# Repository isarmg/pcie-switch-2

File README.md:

# PCIe switch PCB 设计草案

本仓库保存 KiCad 工程、封装、三维模型、生成及检查脚本，以及历次设计版本。

## 当前 E1.S 版本：Rev W

- [打开 KiCad 工程](outputs/PCIe_E1S_96x45_USB12mm_RevW/Main_12E1S/Main_12E1S.kicad_pro)
- [PCB 源文件](outputs/PCIe_E1S_96x45_USB12mm_RevW/Main_12E1S/Main_12E1S.kicad_pcb)
- [STEP 模型](outputs/PCIe_E1S_96x45_USB12mm_RevW/Main_12E1S/Main_12E1S.step)
- [设计说明与限制](outputs/PCIe_E1S_96x45_USB12mm_RevW/README.md)
- [当前重新审查](outputs/PCIe_E1S_96x45_USB12mm_RevW/rebuild_review_2026-10-18/README.md)

板框 96 × 45 mm，12 个竖直 E1.S 插槽，中心距 8 mm。按 CPU/switch 面看，主要顺序为左侧 USB-C、中部 CPU、右侧 switch；供电 USB-C 中心距左板边 12 mm，雷电口为 24 mm，两口中心距 12 mm，均位于板高 22.5 mm。

CPU 为 Ultra 9 288V / 32 GB 封装内存版本；switch 使用经授权虚构的 PEX90064 球位及 33 × 33 mm 封装。雷电电路仍采用雷电 3 主机口方案。32 层叠层和过孔结构是布局布线假设。

历史第一轮的本地电气修订见 [历史审查](outputs/PCIe_E1S_96x45_USB12mm_RevW/ELECTRICAL_REVIEW_2026-10-18.md)。新增全焊盘检查发现旧电源报告仅覆盖选定焊盘，不能证明整网连通；历史报告不再作为当前板通过验证的依据。当前仍有未连接网络和跨层差分对，尚未完成电气与高速设计。已有 STEP 和预览图片尚未随本轮电气修改重新导出，只代表历史几何。

**该工程尚不能直接生产或上电。** 真实 CPU 动态供电、完整雷电内部供电和固件尚未完成，自定义供电 USB-C 尚未接入主输入。SSD 的 12 V / 300 W 是设计预算，不能当作已验证的载流额定值。虚构 switch 不能用于真实芯片贴装；PCIe/雷电信号完整性、阻抗、热、时序与制造要求尚未验证。

当前 E1.S 从保留的第一轮源重新审查，先前未推送的后续本地快照已丢失，不能视为仓库成果。最新已验第三组补齐复位局部/上游连通并修正R725偏置争用，仍有104断网；源 SHA 和独立审计入口见 CURRENT_DESIGNS.json。

## 独立全 M.2 版本

[Rev P / Main_20M2](outputs/PCIe_AllM2_RevP/Main_20M2/Main_20M2.kicad_pro)：120 × 45 mm、20 个 M.2 插槽、中心距 6 mm。其具体实现程度与限制见该版本说明，不能将其与 Rev W 的检查结果混用。

## 目录与使用

- `CURRENT_DESIGNS.json`：当前设计入口和版本信息。
- `outputs/`：KiCad 源文件、项目内封装/符号/模型、检查报告及历次版本。
- `scripts/`：各版本的生成、调整、路由与检查脚本。

用本机 KiCad 10 打开对应 `.kicad_pro`。STEP 模型和工程内库随各版本保存。生成脚本记录了本机工作路径，部分路由脚本还依赖 NumPy、SciPy 和未提交的中间文件；它们不是跨平台的一键构建系统。

下载的厂家数据手册、原始设计套件、工作目录、压缩包和本机 CAD 自动导入文件不在公共提交范围。所需的资料来源与器件参考链接见各版本设计说明；PCB 草案不依赖随仓库分发这些原始下载文件才能在 KiCad 中打开。

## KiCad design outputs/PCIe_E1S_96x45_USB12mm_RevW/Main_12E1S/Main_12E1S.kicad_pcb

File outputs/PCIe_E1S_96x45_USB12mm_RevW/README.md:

当前重新审查已到第三组：复位区域重布局及上游连通、R725偏置争用修正已合入，最新源与限制见[审查入口](rebuild_review_2026-10-18/README.md)。旧STEP/截图尚未重导。

# 当前重审状态

[最新重审记录](rebuild_review_2026-10-18/README.md)：从保留的第一轮源重新构建；现有107个非NC断网，尚不可生产或上电。后续历史本地成果未发布且快照已丢失，不在本次源中。以下为保留的第一轮设计背景与限制。

# Rev W：按 CPU / switch 面调整 USB-C

> 2026-10-18 电气复核已更新源文件；下述旧检查数字为历史记录。请先看 [本轮电气复核](ELECTRICAL_REVIEW_2026-10-18.md) 和 `review_2026-10-18/final_native/` 的最新原生报告，旧报告不能证明当前整板通过。STEP/图片未按本轮局部电路 ECO 重导，只能作历史机械参考。

板框保持 **96 × 45 mm**。从 CPU / switch 面看，供电 USB-C 中心距左板边 **12 mm**，雷电 USB-C 中心距左板边 **24 mm**，两口中心距 **12 mm**，均位于板高 **22.5 mm**。两口保持竖直安装及贴片固定脚。主要顺序为左侧 USB-C、中部 CPU、右侧 switch。

KiCad 正面坐标与此视图的 X 方向相反：J401=(84,22.5)，J402=(72,22.5)，CPU=(54.5,22.5)，switch=(20,22.5)。CPU 中心距此视图左边 41.5 mm，switch 为 76 mm。

打开 `Main_12E1S/Main_12E1S.kicad_pro`。`USB_12mm_CPU_Switch_View.png` 给出中心尺寸，`Main_12E1S/bottom.png` 是本机 KiCad 的 CPU / switch 面三维预览，`Main_12E1S/Main_12E1S.step` 为原生导出模型。

保留 12 个竖直 E1.S、8 mm 中心距和插入后名义侧边距 7.25 mm；无 M.2、小板、安装孔或连接器定位孔，未装入 SSD 三维模型。原连接器模型带下伸结构，移除板孔的草案仍需要最终连接器机械方案。CPU 为 Ultra 9 288V / 32GB；switch 仍为经授权虚构的 PEX90064，33 × 33 mm、1024 个球位，不能用于真实芯片贴装。

## 本次供电进展

保留原 12 V 输入及 12 路 SSD eFuse，每槽 25 W、共 300 W；J101/J102 是来自同一稳压 12 V 电源的两组正负焊线输入，各按 20 A 作预算。自定义供电 USB-C 继续与主输入隔离，尚无可核实的大电流接插件额定值。不能把它当作已完成的 300 W USB 输入。

新增 switch 参考电源来自 PEX88096 资料的保守电流预算，未因虚构芯片删减 lane 而缩小容量：0.9 V 域参考电流 37.427 A，1.8 V 域参考电流 6.903 A。0.9004 V 使用 TPS548D22RVFR（40 A IC），1.8 V 使用 TPSM63610RDFR（8 A IC）；两组模拟域经独立低 DCR 电感滤波，保持原四组电源网络。

TPS548D22 按 650 kHz / FCCM / DCAP3 / 2 ms 软启动配置，FSEL、VSEL、MODE 均包含必需的 BP 端 100 kΩ 上拉，低端分别 22.1 kΩ、33.2 kΩ、47.5 kΩ；ILIM 137 kΩ。输入欠压分压 100 kΩ / 18.2 kΩ，名义启动约 10.39 V。0.16 µH 主电感 XAL7070-161MEC 高 7 mm，位于连接器面；它的温升额定值和实板散热仍需验证。低 DCR 模拟滤波电感采用 XEL4020-101MEC 参考。

1.8 V 模块使用 100 kΩ / 125 kΩ 反馈、100 pF 前馈，400 kHz、强制 PWM、关闭扩频，RBOOT/CBOOT 间为 100 Ω。输出配置 2 × 220 µF 聚合物及 47 µF 陶瓷，实际有效电容须满足 TI 的 350 µF 下限并完成环路、启动和负载瞬态验证。封装依据所附 TI RDF0022A 图绘制，保留端部焊盘的缺口和非等距位置。

In5/In6 保留为两组 12 V 母线专用层；In19/In22 为 switch 0.9 V / 模拟 0.9 V，In4/In7 为 1.8 V / 模拟 1.8 V 专用层。32 层、盲孔和铜厚仍是假定叠层。IC 标称电流及布线连通不等于 PCB、过孔、电源线或接插件已达到额定载流量。

内层示意信号线使用 0.08–0.10 mm 临时宽度；高速差分线尚未按真实叠层完成阻抗、耦合、长度、损耗与过孔优化。部分 P/N 位于不同内层，连通验证不表示达到 PCIe 或雷电电气要求。

In3 另外保留给两组 12 V 输入分区，In2/In30 保留给 3.3 V 辅助电源。槽位及辅助电源的跨层连接完成的是铜箔连通示意；密集区部分铜岛连接以 0.10 mm 细颈接入较宽主线，不能据此认定达到每槽 25 W。仍需依据实板铜厚、温升和压降重新调整这些走线、过孔及供电平面。

## 保留的限制

根据用户选择，CPU 保留真实 200V 系列球位与电源域，未虚构 PMIC 引脚。RAA225019 公开短资料不足以实现完整球位、OTP 和动态电源配置，CPU 动态供电、时序、BIOS 及启动设计仍待完成。

雷电 USB-C 电路沿用用户先前选择的 **雷电 3 主机口**（Alpine Ridge DP + TPS65982），本次没有升级到雷电 4。控制器其余内部电源分配、固件、NVM 和兼容性仍待核实。不得因位置要求中使用“雷电4”称呼便认定已有 TB4 功能。

`VALIDATION.json`、`POWER_CONNECTIVITY.json`、`USB_POSITION_VERIFICATION.json`、`Main_12E1S/DRC.json` 和 STEP 检查均为历史记录，不能证明当前文件已通过。旧供电报告只检查选定 pad_stitches，重复记录和遗漏地脚使“已实现网络连通通过”的旧结论失效。STEP/截图未按本轮 ECO 重导，不代表当前局部电路和铜箔。

## 2026-10-18 本轮结果

- 电气符号补充有资料依据的电源/复位类型；原生 sexpr 网表同步内部网名和自动 NC 名，逐网验证网类。
- U605 保持 3.3 V 辅助供电，MR 改接 U511 的 3.3 V CPU PERST 译码输出，新增 C9040 100 nF 和 R9040 10 kΩ 下拉。局部去耦/下拉已有铜线；MR 至 U511 长支线仍未布通，普通贯孔候选因板边/铜间距冲突撤回，不能称复位电路功能完成。
- USB2 TOP P/N 改为同 In27 短路径，长度差 137.808→0.068814 mm；参考地仍有割裂，SI 未完成。
- 增加 6 个相邻层地孔和 2 个普通贯孔；8 个目标 pad 真接主 GND 簇，GND 156→147 簇。98 个深盲孔候选未并入。
- 全 pad 审计覆盖 6624 个 pad 形状/6558 个唯一 ref.pin，仍有 107 个断裂网络、141 个 P/N 跨层段。499 条原生未连报告可能被工具截断，不能当完整总数。

本轮原生 ERC、完整 track DRC、schematic parity 和源 SHA-256 见 [final_native/REVIEW.json](review_2026-10-18/final_native/REVIEW.json)，全 pad 真连通见 [NATIVE_ALL_PAD_AUDIT.json](NATIVE_ALL_PAD_AUDIT.json)，局部验证见 [ECO_VERIFICATION.json](ECO_VERIFICATION.json)。完整依据、已拒绝方案和剩余阻塞见 [电气复核](ELECTRICAL_REVIEW_2026-10-18.md)。真实 switch 球位、CPU 动态电源、复位重布局、厂商确认叠层/孔工艺、高速 SI 和热/电源完整性仍是必要前提。工程不能生产或上电。

在仓库根目录使用 KiCad 10 Python 运行：

```text
<KiCad10-python> scripts/revW/w_native_audit.py
<KiCad10-python> scripts/revW/w_verify_eco.py
python scripts/revW/w_native_review.py --kicad-cli "<KiCad10 CLI命令>" --output-dir <全新目录> --pad-audit outputs/PCIe_E1S_96x45_USB12mm_RevW/NATIVE_ALL_PAD_AUDIT.json
```

验收入口保留真实失败：原生发现导致退出 2，工具/源文件变化/审计过期导致退出 3；不能以 0 个几何错误代替 ERC、全网连通或制造合格。

供电器件资料：

- [TI TPS548D22](https://www.ti.com/lit/ds/symlink/tps548d22.pdf)
- [TI TPSM63610](https://www.ti.com/lit/ds/symlink/tpsm63610.pdf)
- [Coilcraft XAL7070](https://www.coilcraft.com/en-us/products/power/shielded-inductors/molded-inductor/xal/xal7070/)
- [Coilcraft XEL4020](https://www.coilcraft.com/en-us/products/power/shielded-inductors/molded-inductor/xel/xel4020/)
- [Renesas RAA225019 公开短资料](https://www.renesas.com/en/document/sds/raa225019-short-form-datasheet)

复位链额外断点：最终全 pad 审计中，`PEX_SYS_RESET_N` 有 3 个物理簇、`PEX_RESET_CT` 有 2 个物理簇、`TBT_PCIE_PERST_3V3_N` 有 2 个物理簇。除了新增 MR 长支线待布，原有 RESET 输出和 CT 定时路径也未闭合，需整条复位链重新布线验证。

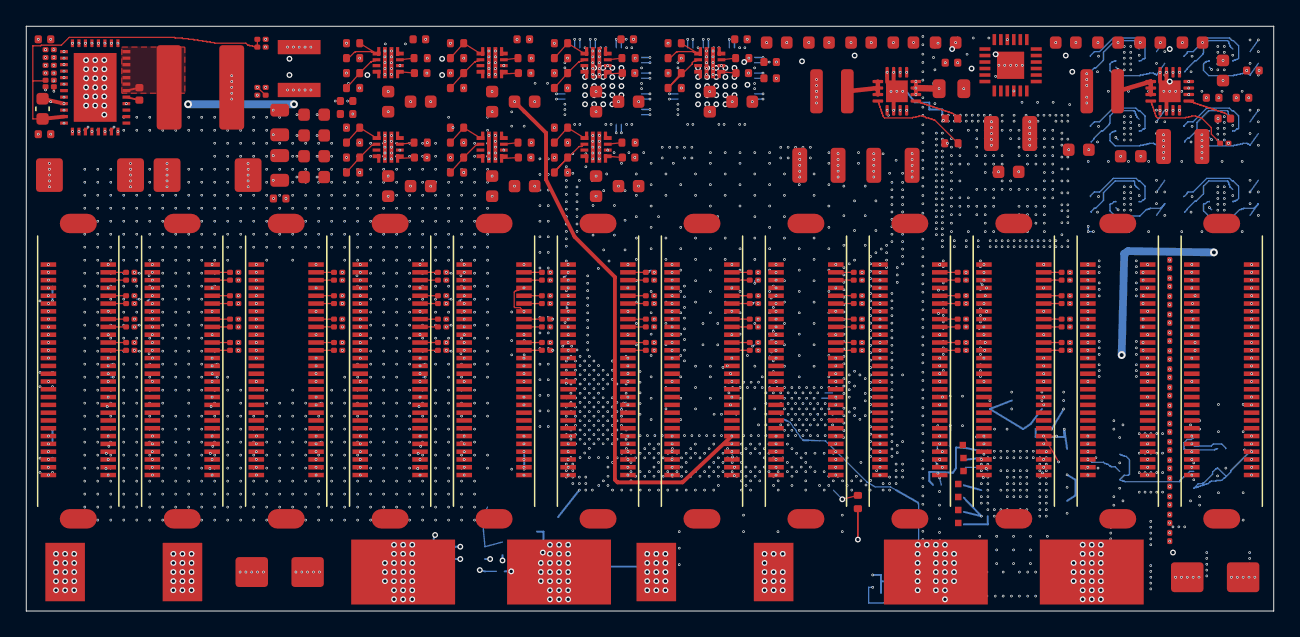
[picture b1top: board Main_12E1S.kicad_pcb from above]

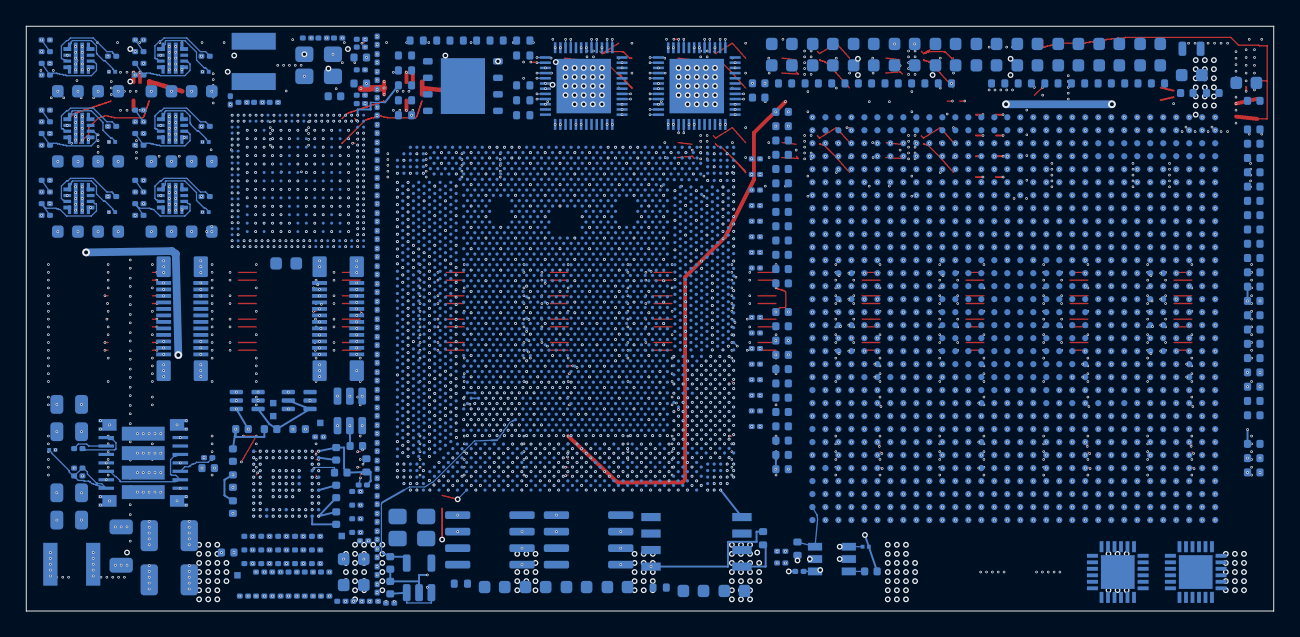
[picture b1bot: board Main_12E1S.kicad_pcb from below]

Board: 32 copper layers, 96.0 x 45.0 mm, 584 parts (334 on the bottom side), 715 nets.

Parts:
C1, C2: 10uF 25V X7R; C_1210_3225Metric
C101, C104, C107, C119, C122, C125: 10nF 25V; C_0201_DenseCourtyard_1p0x0p4
C102, C105, C108, C111, C114, C117, C120, C123, C126, C129: 100nF 50V; C_0603_1608Metric
C103, C106, C109, C112, C115, C118, C121, C124, C127, C130, C133, C136: 10uF 25V X7R / effective >=1uF; C_0603_1608Metric
C110, C113, C116, C128, C131, C134, C301: 10nF 25V; C_0402_1005Metric
C311: 10uF 25V; C_0805_2012Metric
C312: 100nF 50V; C_0402_1005Metric
C313: 3.3nF 25V; C_0402_1005Metric
C314, C315: 47uF 16V; C_1210_3225Metric
C701, C720, C721, C722, C723, C724, C725, C726, C727, C728, C730, C731, C732, C733, C734, C735, C736, C737, C738, C742, C5101, C5102, C5156, C5157, C5158, C5159, C5160: 100nF; C_0402_1005Metric
C702, C707, C708: 1uF; C_0402_1005Metric
C703, C704: 18pF DNP TUNE; C_0402_1005Metric
C705, C706: 8.2pF DNP TUNE; C_0402_1005Metric
C709, C710: 100nF RC reset draft; C_0402_1005Metric
C741: 47nF / reset delay; C_0402_1005Metric
C801, C802, C803, C804, C805, C806, C807, C808, C811, C812, C813, C814, C815, C816, C817, C818: 220nF 16V / GRM033R61C224KE14D; C_0201_0603Metric
C901, C903, C905, C907, C909, C911, C913, C915, C917, C919, C921, C923, C925, C927, C929, C931, C933: 100nF / PDN budget; C_0402_1005Metric
C902, C904, C906, C908, C910, C912, C914, C916, C918, C920, C922, C924, C926, C928, C930, C932, C934: 4.7uF / PDN budget; C_0603_1608Metric
C951, C952, C953, C954, C955, C956, C957, C958, C959, C960: 4.7uF / EDGECAP value pending PDG; C_0603_1608Metric
C965, C966, C967, C968: 1uF / filter value pending PDG; C_0402_1005Metric
C4001, C4002, C4003, C4004, C4005, C4006, C4007, C4008, C4009, C4010, C4011, C4012, C4013, C4014, C4015, C4016, C4017, C4018, C4019, C4020, C4021, C4022, C4023, C4024, C4025, C4026, C4027, C4028, C4029, C4030, C4031, C4032, C4033, C4034, C4035, C4036, C4037, C4038, C4039, C4040, C4041, C4042, C4043, C4044, C4045, C4046, C4047, C4048, C4049, C4050, C4051, C4052, C4053, C4054, C4055, C4056, C4057, C4058, C4059, C4060, C4061, C4062, C4063, C4064, C4065, C4066, C4067, C4068, C4069, C4070, C4071, C4072, C4073, C4074, C4075, C4076, C4077, C4078, C4079, C4080, C4081, C4082, C4083, C4084, C4085, C4086, C4087, C4088, C4089, C4090, C4091, C4092, C4093, C4094, C4095, C4096: 220nF 16V / GRM033R61C224KE14D; C_0201_0603Metric_DenseCourtyard_1p30x0p55
C5110, C5111: 10uF 6.3V; C_0603_1608Metric
C5112, C5113, C5114: 2.2uF 10V 10% X7R; C_0402_1005Metric
C5115: 1uF 6.3V; C_0402_1005Metric
C5116: 220nF; C_0402_1005Metric
C5117: 4.7uF 10V; C_0603_1608Metric
C5118: 2.2uF 25V / effective >=0.5uF at 5V required; C_0402_1005Metric
C5119, C5120: 330pF 25V; C_0402_1005Metric
C5131, C5132, C5133, C5134, C5135, C5136, C5137, C5138, C5139, C5140, C5141, C5142, C5143, C5144: 100nF 6.3V; C_0402_1005Metric
C5151: 22uF 6.3V / SVR output provisional; C_0603_1608Metric
C5152: 4.7uF 6.3V; C_0603_1608Metric
C5153, C5154: 20pF C0G; C_0402_1005Metric
C5155: 10nF / approx 57.6ms; C_0402_1005Metric
C5161: 10uF 25V; C_0603_1608Metric
C5162, C9003: 100nF 25V; C_0402_1005Metric
C5163: 22uF 10V; C_0603_1608Metric
C5164: 3.3nF; C_0402_1005Metric
C5201, C5202, C5203, C5204, C5205, C5206, C5207, C5208, C5209, C5210, C5211, C5212, C5213, C5214, C5215, C5216: 220nF 16V; C_0201_0603Metric_DenseCourtyard_1p30x0p55
C5217, C5218, C5219, C5220, C5221, C5222, C5223, C5224, C5225, C5226, C5227, C5228, C5229, C5230, C5231, C5232: 100nF 16V; C_0201_0603Metric_DenseCourtyard_1p30x0p55
C9001, C9002, C9021, C9022: 22uF 25V X7R; C_0805_2012Metric
C9004: 4.7uF 10V X7R / GRM188Z71A475KE15D; C_0603_1608Metric_BP_Official
C9005: 1uF 25V; C_0402_1005Metric
C9006: 100nF 25V BOOT; C_0402_1005Metric
C9011, C9012: T520D477M2R5ATE009 / 470uF 2.5V / ESR9mOhm; CP_EIA-7343-31_Kemet-D
C9013, C9014, C9015, C9016: 22uF 6.3V X5R / verify effective C; C_0603_1608Metric
C9023, C9024: T520B227M006ATE025 / 220uF 6.3V / ESR25mOhm; CP_EIA-3528-21_Kemet-B
C9025: 47uF 6.3V X7R; C_1206_3216Metric
C9026, C9027: 22uF 6.3V X7R; C_0805_2012Metric
C9028: 100nF / VLDOIN bypass; C_0402_1005Metric
C9029: 100pF C0G / FB feedforward; C_0201_DenseCourtyard_1p0x0p4
C9040: 100nF 6.3V X5R / U605 local bypass; C_0201_DenseCourtyard_1p0x0p4
C9101, C9102, C9103, C9104, C9105, C9106, C9107, C9108, C9109, C9110, C9111, C9112, C9130: 1uF 25V X7R; C_0603_1608Metric
C9131: 10uF 25V X7R; C_0603_1608Metric
D1, D2: SMBJ13CA; D_SMB
F1, F2: 0456025.ER / 25A / derate with temperature; Littelfuse_456_20A
J1, J2, J3, J4, J5, J6, J7, J8, J9, J10, J11, J12: HSEC6-028-01-S-DV-WT-TR; Samtec_HSEC6-028-01-S-DV-WT
J101: 12V INPUT A / 20A budget / solder cable; WireSolder_2x_8x5_P12
J102: 12V INPUT B / 20A budget / solder cable; WireSolder_2x_8x5_P12
J401: CUSTOM POWER USB-C / ISOLATED / INPUT RATING UNVE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; USB_C_24P_Vertical_SMT_Shell_7p46_CUSTOM_DRAFT
J402: THUNDERBOLT 3 HOST / VERTICAL SMT SHELL DRAFT; USB_C_24P_Vertical_SMT_Shell_7p46_CUSTOM_DRAFT
L31, L502: XAL4020-222MEC / 2.2uH / DCR max 38.7mOhm / Isat3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; L_Coilcraft_XAL4020-XXX
L501: 0.68uH / Isat >=2.5A @ <10% drop / select part; INDUCTOR_4x4_LowProfile_DRAFT
L901: XAL7070-161MEC / 0.16uH / thermal validation requ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; L_Coilcraft_XAL7070-XXX
L902, L903: XEL4020-101MEC / 0.1uH / DCRmax2.5mOhm; L_XEL4020_Land_4p5x4p1
R101, R106, R111, R131, R136, R141: 76.1k; R_0201_DenseCourtyard_1p0x0p4
R102, R104, R107, R109, R112, R114, R132, R134, R137, R139, R142, R144, R5128, R5131, R5132, R5133, R5141, R5142, R5143, R5144, R5155, R5156, R5181, R5191, R5192, R5193: 10k; R_0201_DenseCourtyard_1p0x0p4
R103, R108, R113, R133, R138, R143: 102k; R_0201_DenseCourtyard_1p0x0p4
R105, R110, R115, R135, R140, R145: 1.10k; R_0201_DenseCourtyard_1p0x0p4
R116, R121, R126, R146, R151, R156, R301: 76.1k; R_0402_1005Metric
R117, R119, R122, R124, R127, R129, R147, R149, R152, R154, R157, R159, R302, R304, R702, R703, R704, R712, R713, R724, R725: 10k; R_0402_1005Metric
R118, R123, R128, R148, R153, R158, R303: 102k; R_0402_1005Metric
R120, R125, R130, R150, R155, R160: 1.10k; R_0402_1005Metric
R305: 750R 1% / AUX limit 4.45A nominal; R_0402_1005Metric
R311, R401, R402, R710, R711: 100k; R_0402_1005Metric
R701: 22R provisional SI tuning; R_0402_1005Metric
R705: 180R 1% / Intel clock topology; R_0402_1005Metric
R706, R707: TBD RCOMP / DNP / Intel PDG required; R_0402_1005Metric
R708, R709: 200R 1%; R_0402_1005Metric
R714, R715, R716: 0R / request clock always on; R_0402_1005Metric
R721, R722: 0R analog supply link / filter pending; R_0402_1005Metric
R730, R731, R732: DNP / filter link pending Intel PDG; R_0402_1005Metric
R740, R741, R742, R744, R745, R746: 10k / Intel required external bias; R_0402_1005Metric
R743: 4.7k 1% / Intel WAKE external bias; R_0402_1005Metric
R5101, R9021: 100R; R_0201_DenseCourtyard_1p0x0p4
R5102, R5103: 4.75k 0.5%; R_0201_DenseCourtyard_1p0x0p4
R5104: 3.01k 1%; R_0201_DenseCourtyard_1p0x0p4
R5105, R5106: 14k 1%; R_0201_DenseCourtyard_1p0x0p4
R5107, R5108: 499R 1%; R_0201_DenseCourtyard_1p0x0p4
R5111, R5112, R5113, R5114, R5153, R5154, R5194, R9007, R9024: 100k; R_0201_DenseCourtyard_1p0x0p4
R5121, R5122, R5123, R5124, R5125: 10k / always-on host strap; R_0201_DenseCourtyard_1p0x0p4
R5151: 15k 0.1%; R_0402_1005Metric
R5152: 0R / I2C address strap; R_0201_DenseCourtyard_1p0x0p4
R5161, R5162, R5163, R5164, R5165, R5166, R5167, R5168, R5169, R5170, R5171, R5172, R5173, R5174, R5175: 1M / firmware strap review; R_0201_DenseCourtyard_1p0x0p4
R9001: 22.1k 1% / 650kHz FCCM; R_0201_DenseCourtyard_1p0x0p4
R9002: 33.2k 1% / 0.9004V; R_0201_DenseCourtyard_1p0x0p4
R9003: 47.5k 1% / 2ms SS; R_0201_DenseCourtyard_1p0x0p4
R9004: 137k 1% / 43.2A valley; R_0201_DenseCourtyard_1p0x0p4
R9005: 100k 1%; R_0201_DenseCourtyard_1p0x0p4
R9006: 18.2k 1% / UVLO nominal10.39V; R_0201_DenseCourtyard_1p0x0p4
R9008: 0R / remote sense at switch; R_0201_DenseCourtyard_1p0x0p4
R9009: 0R / remote return at switch; R_0201_DenseCourtyard_1p0x0p4
R9011, R9012, R9013: 100k 1% / mandatory upper strap; R_0201_DenseCourtyard_1p0x0p4
R9022: 100k 0.1%; R_0201_DenseCourtyard_1p0x0p4
R9023: 125k 0.1%; R_0201_DenseCourtyard_1p0x0p4
R9040: 10k 1% / reset fail-low; R_0201_DenseCourtyard_1p0x0p4
R9041: 10k 1% / PEX flash CS pull-up; R_0402_1005Metric
TP701: PROBE /CPU_SVID_CLK_1V25; Probe_0p5mm
TP702: PROBE /CPU_SVID_DATA_1V25; Probe_0p5mm
TP703: PROBE /CPU_SVID_ALERT_1V25_N; Probe_0p5mm
TP704: PROBE /CPU_PLT_PWROK; Probe_0p5mm
TP705: PROBE /CPU_SYS_PWROK_1V8; Probe_0p5mm
TP706: PROBE /CPU_RSMRST_N; Probe_0p5mm
TP707: PROBE /CPU_SYS_RESET_1V8_N; Probe_0p5mm
TP708: PROBE /CPU_PWRBTN_1V8_N; Probe_0p5mm
TP709: PROBE /CPU_VCCST_EN_1V8; Probe_0p5mm
TP710: PROBE /CPU_SLP_S3_1V8_N; Probe_0p5mm
TP711: PROBE /CPU_SLP_S4_1V8_N; Probe_0p5mm
TP712: PROBE /CPU_SLP_S5_1V8_N; Probe_0p5mm
U1: PEX90064 / FAKE 64-lane 33x33 BGA1024; PEX90064_FAKE_BGA1024_33x33_P1_Reordered_NOT_REAL
U11, U12, U13, U14, U15, U16, U17, U18, U19, U20, U21, U22, U30: TPS259470ARPWR; TI_RPW0010A_TPS25947
U31: TPS62132RGTR; VQFN-16-1EP_3x3mm_P0.5mm_EP1.68x1.68mm
U501: DSL6540 / Alpine Ridge DP / TB3 HOST / NVM pending; ALPINE_RIDGE_DP_BGA337_MixedPitch_10p7x10p7
U502: Intel Core Ultra 9 288V / 32GB LPDDR5X MoP / BGA2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; Intel_Core_Ultra_200V_BGA2833_27p5x27_ExactXY_DraftLands
U503: TPS65982 / Type-C DFP / 5V3A source / NVM pending; TI_TPS65982_BGA96_6x6_P0p5
U504, U505: W25Q80DVSNJG / 3.3V 8Mbit NVM / image pending; SOIC-8_3.9x4.9mm_P1.27mm
U506: TPS62133RGTR / 12V to 5V 3A USB source; VQFN-16-1EP_3x3mm_P0.5mm_EP1.68x1.68mm
U510: TPS3808G33DBVR / AR reset delay; SOT-23-6
U511: SN74AXC1T45DCKR / PERST 1.8V to 3.3V; SOT-363_SC-70-6
U512: SN74AXC1T45DCKR / HPDA 3.3V to 1.8V; SOT-363_SC-70-6
U601: 9ZXL0851EKILFT / CPU common clock 100MHz; REF_9ZXL0851EKILFT_KU1
U602: 9ZXL0851EKILFT / CPU common clock 100MHz; REF_9ZXL0851EKILFT_KU3
U603: 9FGV0241AKLF / DNP ALTERNATE CLOCK; REF_9FGV0241AKLF_KU2
U604: 9DML0451AKILF / DNP ALTERNATE CLOCK; REF_9DML0451AKILF_KU5
U605: TPS3808G09DBVR / SUPPORT NETWORK PENDING; REF_TPS3808G09DBVR_FU1
U606: W25Q32JWSSIQ_C2980995 / SUPPORT NETWORK PENDING; REF_W25Q32JWSSIQ_FU2
U607: TCA9548ARGER / SUPPORT NETWORK PENDING; REF_TCA9548ARGER_SU1
U701: W25Q256JWPIQ / 1.8V 32MiB BIOS; WSON-8-1EP_6x5mm_P1.27mm_EP3.4x4.3mm
U702: TPS7A0215PDBVR / RTC 1.5V; SOT-23-5
U901: TPS548D22RVFR / 0.9004V 40A reference; TI_RVF0040A_TPS548D22
U902: TPSM63610RDFR / 1.8V 8A; TI_RDF0022A_TPSM63610_NotchedLand
Y501: 25MHz / 20pF / 30ppm / ESR <=50R / select part; Crystal_SMD_3225-4Pin_3.2x2.5mm
Y701: 38.4MHz crystal / load and ESR selection pending; Crystal_SMD_3225-4Pin_3.2x2.5mm
Y702: 32.768kHz crystal / load and ESR selection pending; Crystal_SMD_2012-2Pin_2.0x1.2mm

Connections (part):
/AUX_12V_PROTECTED: C311.1, C312.1, C5161.1, C5162.1, C9131.1, U30.6, U31.10, U31.11, U31.12, U31.13, U506.10, U506.11, U506.12, U506.13
/AUX_DVDT: C301.1, U30.7
/AUX_ILM: R305.1, U30.9
/AUX_OV: R303.2, R304.1, U30.2
/AUX_PG: R311.2, U31.4
/AUX_UV: R301.2, R302.1, U30.1
/BUCK_SS: C313.1, U31.9
/BUCK_SW: L31.1, U31.1, U31.2, U31.3
/CLKBUF1_VDDA: C728.1, R721.2, U601.44
/CLKBUF2_VDDA: C738.1, R722.2, U602.44
/CPU_ACPRESENT: R741.1, U502.P45
/CPU_BATLOW_N: R740.1, U502.R50
/CPU_CLKBUF1_IN_N: U502.BC2, U601.5
/CPU_CLKBUF1_IN_P: U502.BB1, U601.4
/CPU_CLKBUF2_IN_N: U502.AY4, U602.5
/CPU_CLKBUF2_IN_P: U502.AW3, U602.4
/CPU_CLKREQ0_N: R714.1, U502.B55
/CPU_CLKREQ1_N: R715.1, U502.F50
/CPU_CLKREQ2_N: R716.1, U502.E51
/CPU_CLK_RCOMP: R705.1, U502.BG3
/CPU_EPD_ON_LOOP_1V25: U502.AB27, U502.Y27
/CPU_G5_RX0_N: C812.2, U502.DD16
/CPU_G5_RX0_P: C811.2, U502.DE14
/CPU_G5_RX1_N: C814.2, U502.DA18
/CPU_G5_RX1_P: C813.2, U502.CY17
/CPU_G5_RX2_N: C816.2, U502.CY22
/CPU_G5_RX2_P: C815.2, U502.DA21
/CPU_G5_RX3_N: C818.2, U502.DC24
/CPU_G5_RX3_P: C817.2, U502.DD23
/CPU_G5_TX0_N: C802.1, U502.DL16
/CPU_G5_TX0_P: C801.1, U502.DK17
/CPU_G5_TX1_N: C804.1, U502.DH17
/CPU_G5_TX1_P: C803.1, U502.DF18
/CPU_G5_TX2_N: C806.1, U502.DH22
/CPU_G5_TX2_P: C805.1, U502.DF21
/CPU_G5_TX3_N: C808.1, U502.DL23
/CPU_G5_TX3_P: C807.1, U502.DK22
/CPU_PCIE4_RCOMP: R706.1, U502.DL39
/CPU_PCIE5_RCOMP: R707.1, U502.DA1
/CPU_PERST_1V8_N: R725.1, U1.AM32, U502.F24, U511.3
/CPU_PEX_RX0_N: C802.2, U1.AD32
/CPU_PEX_RX0_P: C801.2, U1.AC32
/CPU_PEX_RX1_N: C804.2, U1.AA32
/CPU_PEX_RX1_P: C803.2, U1.Y32
/CPU_PEX_RX2_N: C806.2, U1.V32
/CPU_PEX_RX2_P: C805.2, U1.U32
/CPU_PEX_RX3_N: C808.2, U1.R32
/CPU_PEX_RX3_P: C807.2, U1.P32
/CPU_PEX_TX0_N: C812.1, U1.M32
/CPU_PEX_TX0_P: C811.1, U1.L32
/CPU_PEX_TX1_N: C814.1, U1.J32
/CPU_PEX_TX1_P: C813.1, U1.H32
/CPU_PEX_TX2_N: C816.1, U1.F32
/CPU_PEX_TX2_P: C815.1, U1.E32
/CPU_PEX_TX3_N: C818.1, U1.C32
/CPU_PEX_TX3_P: C817.1, U1.B32
/CPU_PLT_PWROK: R745.1, TP704.1, U502.H13
/CPU_PMCALERT_N: R742.1, U502.F42
/CPU_PWRBTN_1V8_N: R713.1, TP708.1, U502.P47
/CPU_REFCLK_N: U1.AH32, U502.BC4
/CPU_REFCLK_P: U1.AG32, U502.BB3
/CPU_RSMRST_N: R744.1, TP706.1, U502.E13
/CPU_RTCRST_N: C709.1, R710.1, U502.H15
/CPU_RTCX1: C705.1, U502.A12, Y702.1
/CPU_RTCX2: C706.1, U502.A10, Y702.2
/CPU_SLP_S3_1V8_N: TP710.1, U502.M44
/CPU_SLP_S4_1V8_N: TP711.1, U502.L55
/CPU_SLP_S5_1V8_N: TP712.1, U502.P53
/CPU_SPI_CLK_FLASH: R701.2, U701.6
/CPU_SPI_CLK_PAD: R701.1, U502.W13
/CPU_SPI_CS0_N: R702.1, U502.AC17, U701.1
/CPU_SPI_IO0: U502.AA17, U701.5
/CPU_SPI_IO1: U502.AE17, U701.2
/CPU_SPI_IO2: R703.1, U502.W17, U701.3
/CPU_SPI_IO3: R704.1, U502.U13, U701.7
/CPU_SRTCRST_N: C710.1, R711.1, U502.B15
/CPU_SVID_ALERT_1V25_N: TP703.1, U502.F56
/CPU_SVID_CLK_1V25: TP701.1, U502.E55
/CPU_SVID_DATA_1V25: TP702.1, U502.C56
/CPU_SYS_PWROK_1V8: R746.1, TP705.1, U502.H31
/CPU_SYS_RESET_1V8_N: R712.1, TP707.1, U502.M52
/CPU_USB2_RCOMP: R708.1, U502.W1
/CPU_USB32_RCOMP: R709.1, U502.BG1
/CPU_V1P8U_MEM: C901.1, C902.1, U502.AK67, U502.AK70, U502.AL69, U502.AM67, U502.AM70, U502.AP67, U502.AP70, U502.AR69, U502.AT67, U502.AT70, U502.AT73, U502.AT76, U502.AT79, U502.AU69, U502.AU75, U502.AU80, U502.AV67, U502.AV70, U502.AV73, U502.AV76, U502.AV79, U502.AW69, U502.AW72, U502.AW75, U502.AW77, U502.AW80, U502.AY67, U502.AY70, U502.AY73, U502.AY76, U502.AY79, U502.BA72, U502.BA77, U502.BB67, U502.BB70, U502.BB73, U502.BB76, U502.BB79, U502.BC69, U502.BC77, U502.BC80, U502.BD67, U502.BD79, U502.BD82, U502.BD85, U502.BD88, U502.BD90, U502.BD93, U502.BE69, U502.BE80, U502.BE86, U502.BF67, U502.BF79, U502.BF82, U502.BF85, U502.BF88, U502.BF90, U502.BF93, U502.BG69, U502.BG77, U502.BG80, U502.BG83, U502.BG86, U502.BG89, U502.BG92, U502.BH67, U502.BH79, U502.BH82, U502.BH85, U502.BH88, U502.BH90, U502.BH93, U502.BJ77, U502.BK67, U502.BK79, U502.BL69, U502.BL72, U502.BL77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
/CPU_V1P8U_MEM_EDGECAP_0: C951.1, U502.B69, U502.B71
/CPU_V1P8U_MEM_EDGECAP_1: C952.1, U502.AE92, U502.AG92
/CPU_V1P8U_MEM_EDGECAP_2: C953.1, U502.CE92, U502.CG92
/CPU_V1P8U_MEM_EDGECAP_3: C954.1, U502.DK68, U502.DK70
/CPU_VCCGT: C903.1, C904.1, U502.A34, U502.A36, U502.A38, U502.A40, U502.A42, U502.A44, U502.A46, U502.A48, U502.A50, U502.A52, U502.A54, U502.A56, U502.A58, U502.A60, U502.A88, U502.A90, U502.AA34, U502.AA40, U502.AA46, U502.AA51, U502.AA57, U502.AA63, U502.AA69, U502.AA75, U502.AA80, U502.AA86, U502.AB30, U502.AB33, U502.AB36, U502.AB38, U502.AB41, U502.AB44, U502.AB47, U502.AB50, U502.AB53, U502.AB56, U502.AB59, U502.AB62, U502.AB64, U502.AB67, U502.AB70, U502.AB73, U502.AB76, U502.AB79, U502.AB82, U502.AB85, U502.AB88, U502.AB90, U502.AB93, U502.AC31, U502.AC34, U502.AC37, U502.AC40, U502.AC43, U502.AC46, U502.AC49, U502.AC51, U502.AC54, U502.AC57, U502.AC60, U502.AC63, U502.AC66, U502.AC69, U502.AC72, U502.AC75, U502.AC77, U502.AC80, U502.AC83, U502.AC86, U502.AC89, U502.AC92, U502.AD30, U502.AD33, U502.AD36, U502.AD38, U502.AD41, U502.AD44, U502.AD47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
/CPU_VCCL2: C905.1, C906.1, U502.BV41, U502.BV44, U502.BV47, U502.BW40, U502.BW43, U502.BW46
/CPU_VCCPRIM_1P8: C701.1, C702.1, C907.1, C908.1, C5157.1, C5159.1, R702.2, R703.2, R704.2, R712.2, R713.2, R725.2, R730.1, R731.1, R740.2, R741.2, R742.2, R743.2, U502.AR20, U502.AR23, U502.AR26, U502.AT21, U502.AT24, U502.AU20, U502.AU23, U502.AU26, U511.1, U511.5, U512.1, U701.8
/CPU_VCCPRIM_1P8_FLTRA_IN: C966.1, R730.2, U502.BJ20, U502.BL20, U502.BN20
/CPU_VCCPRIM_1P8_FLTRB_CAP: C965.1, U502.CN31, U502.CN34, U502.CP30, U502.CP33
/CPU_VCCPRIM_1P8_FLTRB_IN: C967.1, R731.2, U502.AR17, U502.AT18, U502.AU17
/CPU_VCCPRIM_3P3: C909.1, C910.1, U502.AW17, U502.BA17
/CPU_VCCPRIM_IO: C911.1, C912.1, U502.BB18, U502.BC17, U502.BD18, U502.BE17, U502.BF18, U502.BG17, U502.BH18, U502.BJ17, U502.BK18, U502.BL17, U502.BM18, U502.BN17, U502.BP18, U502.BR17, U502.BT18, U502.BU17, U502.BV18, U502.BW17, U502.BY18, U502.CA17, U502.CB18, U502.CC17, U502.CD18, U502.CE17, U502.CF18, U502.CG17, U502.CH18, U502.CJ17, U502.CK18, U502.CL17, U502.CM18, U502.CN17, U502.CN20, U502.CN23, U502.CN26, U502.CN28, U502.CP18, U502.CP21, U502.CP24, U502.CP27
/CPU_VCCPRIM_VNNAON: C913.1, C914.1, R732.1, U502.AW20, U502.AW23, U502.AW26, U502.AY21, U502.AY24, U502.AY27, U502.BA20, U502.BA26, U502.BB21, U502.BB24, U502.BB27, U502.BC20, U502.BC23, U502.BC26, U502.BD21, U502.BD24, U502.BD27, U502.BE23, U502.BF24, U502.BF27, U502.BG23, U502.BG26, U502.BH21, U502.BH24, U502.BJ23, U502.BJ26, U502.BK24, U502.BL23, U502.BL26, U502.BM24, U502.BN23, U502.BP21, U502.BP24, U502.BR20, U502.BR23, U502.BT21, U502.BT24, U502.BU20, U502.BV21, U502.BV24, U502.BW20, U502.BW23, U502.BY21, U502.BY24, U502.CA23, U502.CB21, U502.CB24, U502.CC20, U502.CC23, U502.CD21, U502.CD24, U502.CE20, U502.CF21, U502.CG20, U502.CG23, U502.CH21, U502.CJ23, U502.CK21, U502.CK24, U502.CK27, U502.CK30, U502.CL20, U502.CL23, U502.CL26, U502.CL28
/CPU_VCCPRIM_VNNAONLV: C915.1, C916.1, U502.BK27, U502.BK30, U502.BL28, U502.BM27, U502.BM30, U502.BN28, U502.BP27, U502.BP30, U502.BR26, U502.BR28, U502.BT27, U502.BT30, U502.BU26, U502.BV27, U502.BV30, U502.BW26, U502.BW28, U502.BY27, U502.BY30, U502.CA28, U502.CB27, U502.CB30, U502.CC26, U502.CC28, U502.CD27, U502.CD30, U502.CE26, U502.CF24, U502.CF27, U502.CF30, U502.CG26, U502.CG28, U502.CH24, U502.CH27, U502.CH30, U502.CJ28
/CPU_VCCPRIM_VNNAON_FLTR: C968.1, R732.2, U502.BE20, U502.BG20
/CPU_VCCRTC: C708.1, C917.1, C918.1, R710.2, R711.2, U502.AN20, U702.5
/CPU_VCCSA: C919.1, C920.1, U502.AU34, U502.AU40, U502.AU46, U502.AU51, U502.AV33, U502.AV36, U502.AV38, U502.AV41, U502.AV44, U502.AV47, U502.AV50, U502.AV53, U502.AV56, U502.AW34, U502.AW37, U502.AW40, U502.AW43, U502.AW46, U502.AW49, U502.AW51, U502.AW54, U502.AY33, U502.AY36, U502.AY38, U502.AY41, U502.AY44, U502.AY47, U502.AY50, U502.AY53, U502.AY56, U502.BA31, U502.BA37, U502.BA43, U502.BA49, U502.BA54, U502.BB33, U502.BB36, U502.BB38, U502.BB41, U502.BB44, U502.BB47, U502.BB50, U502.BB53, U502.BB56, U502.BC31, U502.BC34, U502.BC40, U502.BC43, U502.BC46, U502.BC49, U502.BC51, U502.BC54, U502.BD33, U502.BD36, U502.BD38, U502.BD41, U502.BD44, U502.BD47, U502.BD50, U502.BD53, U502.BD56, U502.BE31, U502.BE34, U502.BE37, U502.BE40, U502.BE46, U502.BE51, U502.BF33, U502.BF36, U502.BF38, U502.BF41, U502.BF44, U502.BF47, U502.BF50, U502.BF53, U502.BF56, U502.BG31, U502.BG34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
/CPU_VCCST: C921.1, C922.1, U502.AU31, U502.AV30
/CPU_VCCST_EN_1V8: TP709.1, U502.M48
/CPU_VCC_ECORE: C923.1, C924.1, U502.BJ40, U502.BJ43, U502.BJ46, U502.BK38, U502.BK41, U502.BK44, U502.BK47, U502.BL43, U502.BM38, U502.BM41, U502.BM44, U502.BM47, U502.BN40, U502.BN43, U502.BN46, U502.BP38, U502.BP41, U502.BP44, U502.BP47, U502.BR43, U502.BT38, U502.BT41, U502.BT44, U502.BT47, U502.BU40, U502.BU43, U502.BU46, U502.BV38
/CPU_VCC_PCORE: C925.1, C926.1, U502.CA40, U502.CA46, U502.CA51, U502.CA57, U502.CA63, U502.CB36, U502.CB38, U502.CB41, U502.CB44, U502.CB47, U502.CB50, U502.CB53, U502.CB56, U502.CB59, U502.CB62, U502.CB64, U502.CC37, U502.CC40, U502.CC43, U502.CC46, U502.CC49, U502.CC51, U502.CC54, U502.CC57, U502.CC60, U502.CC63, U502.CC66, U502.CC69, U502.CC72, U502.CC80, U502.CC83, U502.CC86, U502.CD36, U502.CD38, U502.CD41, U502.CD44, U502.CD47, U502.CD50, U502.CD53, U502.CD56, U502.CD59, U502.CD62, U502.CD64, U502.CD67, U502.CD70, U502.CD82, U502.CD85, U502.CD88, U502.CE37, U502.CE43, U502.CE49, U502.CE54, U502.CE60, U502.CE66, U502.CE72, U502.CE83, U502.CE89, U502.CF36, U502.CF38, U502.CF41, U502.CF44, U502.CF47, U502.CF50, U502.CF53, U502.CF56, U502.CF59, U502.CF62, U502.CF64, U502.CF67, U502.CF70, U502.CF73, U502.CF76, U502.CF79, U502.CF82, U502.CF85, U502.CF88, U502.CG37, U502.CG40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
/CPU_VDD2H: C927.1, C928.1, U502.BJ83, U502.BJ89, U502.BK82, U502.BK85, U502.BK88, U502.BK90, U502.BK93, U502.BL83, U502.BL86, U502.BL89, U502.BL92, U502.BM82, U502.BM85, U502.BM88, U502.BM90, U502.BM93, U502.BN86, U502.BP82, U502.BP85, U502.BP88, U502.BP90, U502.BP93, U502.BR83, U502.BR86, U502.BR89, U502.BR92, U502.BT82, U502.BT85, U502.BT88, U502.BT90, U502.BT93
/CPU_VDD2H_EDGECAP_0: C955.1, U502.B81, U502.B83, U502.B86
/CPU_VDD2H_EDGECAP_1: C956.1, U502.DK80, U502.DK82, U502.DK84
/CPU_VDD2L: C929.1, C930.1, U502.AL72, U502.AL80, U502.AL83, U502.AL86, U502.AL89, U502.AL92, U502.AM73, U502.AM76, U502.AM79, U502.AM82, U502.AM85, U502.AM88, U502.AN72, U502.AN77, U502.AN83, U502.AN89, U502.AN92, U502.AP73, U502.AP76, U502.AP79, U502.AP82, U502.AP85, U502.AP88, U502.AR72, U502.AR75, U502.AR77, U502.AR80, U502.AR83, U502.AR86, U502.AR89, U502.AR92, U502.BU72, U502.BU77, U502.BU83, U502.BU89, U502.BU92, U502.BV73, U502.BV76, U502.BV79, U502.BV82, U502.BV85, U502.BV88, U502.BW72, U502.BW75, U502.BW77, U502.BW80, U502.BW83, U502.BW86, U502.BW89, U502.BW92, U502.BY73, U502.BY76, U502.BY79, U502.BY82, U502.BY85, U502.BY88, U502.CA80, U502.CA86, U502.CA89, U502.CA92, U502.CB82, U502.CB85, U502.CB88
/CPU_VDD2L_EDGECAP_0: C957.1, U502.B73
/CPU_VDD2L_EDGECAP_1: C958.1, U502.DK72
/CPU_VDD2_PWRGOOD_LOOP: U502.AA26, U502.AC26
/CPU_VDDQ: C931.1, C932.1, U502.AT82, U502.AT85, U502.AT88, U502.AT90, U502.AT93, U502.AU86, U502.AV82, U502.AV85, U502.AV88, U502.AV90, U502.AV93, U502.AW83, U502.AW86, U502.AW89, U502.AW92, U502.AY82, U502.AY85, U502.AY88, U502.AY90, U502.AY93, U502.BA83, U502.BA89, U502.BB82, U502.BB85, U502.BB88, U502.BB90, U502.BB93, U502.BC83, U502.BC86, U502.BC89, U502.BC92
/CPU_VDDQ_EDGECAP_0: C959.1, U502.B75, U502.B77, U502.B79
/CPU_VDDQ_EDGECAP_1: C960.1, U502.DK74, U502.DK76, U502.DK78
/CPU_VDDRIO: C933.1, C934.1, U502.AR57, U502.AR60, U502.AR63, U502.AR66, U502.AT59, U502.AT62, U502.AT64, U502.AU57, U502.AU63, U502.AV59, U502.AV62, U502.AV64, U502.AW57, U502.AW60, U502.AW63, U502.AW66, U502.AY59, U502.AY62, U502.AY64, U502.BA60, U502.BA66, U502.BB59, U502.BB62, U502.BB64, U502.BC57, U502.BC60, U502.BC63, U502.BC66, U502.BD59, U502.BD62, U502.BD64, U502.BE57, U502.BE63, U502.BF59, U502.BF62, U502.BF64, U502.BG57, U502.BG60, U502.BG63, U502.BG66, U502.BH59, U502.BH62, U502.BH64, U502.BJ60, U502.BJ66, U502.BK59, U502.BK62, U502.BK64, U502.BL57, U502.BL60, U502.BL63, U502.BM59, U502.BM62, U502.BM64, U502.BN57, U502.BN63, U502.BP59, U502.BP62, U502.BP64, U502.BR57, U502.BR60, U502.BR63, U502.BT59, U502.BT62, U502.BT64, U502.BU60, U502.BU66, U502.BV59, U502.BV62, U502.BV64, U502.BW57, U502.BW60, U502.BW63, U502.BW66, U502.BY59, U502.BY62, U502.BY64
/CPU_WAKE_N: R743.1, U502.P49
/CPU_XTAL_IN: C703.1, U502.M1, Y701.1
/CPU_XTAL_OUT: C704.1, U502.N2, Y701.3
/CUSTOM_12V_RAW: J401.A4, J401.A6, J401.A7, J401.A8, J401.A9, J401.B4, J401.B6, J401.B7, J401.B8, J401.B9
/CUSTOM_DET_A: J401.A5, R401.1
/CUSTOM_DET_B: J401.B5, R402.1
/GND: C1.2, C2.2, C101.2, C102.2, C103.2, C104.2, C105.2, C106.2, C107.2, C108.2, C109.2, C110.2, C111.2, C112.2, C113.2, C114.2, C115.2, C116.2, C117.2, C118.2, C119.2, C120.2, C121.2, C122.2, C123.2, C124.2, C125.2, C126.2, C127.2, C128.2, C129.2, C130.2, C131.2, C133.2, C134.2, C136.2, C301.2, C311.2, C312.2, C313.2, C314.2, C315.2, C701.2, C702.2, C703.2, C704.2, C705.2, C706.2, C707.2, C708.2, C709.2, C710.2, C720.2, C721.2, C722.2, C723.2, C724.2, C725.2, C726.2, C727.2, C728.2, C730.2, C731.2, C732.2, C733.2, C734.2, C735.2, C736.2, C737.2, C738.2, C741.2, C742.2, C901.2, C902.2, C903.2, C904.2, C905.2, C906.2, C907.2, C908.2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
/P3V3_AUX: C314.1, C315.1, C707.1, C720.1, C721.1, C722.1, C723.1, C724.1, C725.1, C726.1, C727.1, C730.1, C731.1, C732.1, C733.1, C734.1, C735.1, C736.1, C737.1, C742.1, C5110.1, C5152.1, C5156.1, C5158.1, C5160.1, C9040.1, J1.B11, J2.B11, J3.B11, J4.B11, J5.B11, J6.B11, J7.B11, J8.B11, J9.B11, J10.B11, J11.B11, J12.B11, L31.2, R311.1, R721.1, R722.1, R5121.2, R5122.2, R5123.2, R5124.2, R5125.2, R5128.2, R5131.2, R5132.2, R5133.2, R5181.2, R5191.2, R5192.2, R5193.2, R9007.2, R9024.2, U1.W32, U31.14, U501.A2, U501.A3, U501.B3, U501.F8, U501.H9, U501.R13, U503.H1, U510.5, U510.6, U511.6, U512.6, U601.1, U601.3, U601.10, U601.15, U601.19, U601.27, U601.34, U601.38, U601.42, U601.47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
/P12_SLOT01: C103.1, J1.B1, J1.B2, J1.B3, J1.B4, J1.B5, J1.B6, U11.6
/P12_SLOT02: C106.1, J2.B1, J2.B2, J2.B3, J2.B4, J2.B5, J2.B6, U12.6
/P12_SLOT03: C109.1, J3.B1, J3.B2, J3.B3, J3.B4, J3.B5, J3.B6, U13.6
/P12_SLOT04: C112.1, J4.B1, J4.B2, J4.B3, J4.B4, J4.B5, J4.B6, U14.6
/P12_SLOT05: C115.1, J5.B1, J5.B2, J5.B3, J5.B4, J5.B5, J5.B6, U15.6
/P12_SLOT06: C118.1, J6.B1, J6.B2, J6.B3, J6.B4, J6.B5, J6.B6, U16.6
/P12_SLOT07: C121.1, J7.B1, J7.B2, J7.B3, J7.B4, J7.B5, J7.B6, U17.6
/P12_SLOT08: C124.1, J8.B1, J8.B2, J8.B3, J8.B4, J8.B5, J8.B6, U18.6
/P12_SLOT09: C127.1, J9.B1, J9.B2, J9.B3, J9.B4, J9.B5, J9.B6, U19.6
/P12_SLOT10: C130.1, J10.B1, J10.B2, J10.B3, J10.B4, J10.B5, J10.B6, U20.6
/P12_SLOT11: C133.1, J11.B1, J11.B2, J11.B3, J11.B4, J11.B5, J11.B6, U21.6
/P12_SLOT12: C136.1, J12.B1, J12.B2, J12.B3, J12.B4, J12.B5, J12.B6, U22.6
/PEX09_BOOT: C9006.1, U901.5
/PEX09_BP: C9004.1, R9011.1, R9012.1, R9013.1, U901.31
/PEX09_EN: R9005.2, R9006.1, U901.4
/PEX09_FSEL: R9001.1, R9011.2, U901.32
/PEX09_ILIM: R9004.1, U901.36
/PEX09_MODE: R9003.1, R9013.2, U901.34
/PEX09_PG: R9007.1, U901.35
/PEX09_SENSE_N: R9009.1, U901.38
/PEX09_SENSE_P: R9008.1, U901.39
/PEX09_SW: C9006.2, L901.1, U901.6, U901.7, U901.8, U901.9, U901.10, U901.11, U901.12
/PEX09_VSEL: R9002.1, R9012.2, U901.33
/PEX18_CBOOT: R9021.2, U902.3
/PEX18_FB: C9029.2, R9022.2, R9023.1, U902.8
/PEX18_PG: R9024.1, U902.13
/PEX18_RBOOT: R9021.1, U902.2
/PEX18_VCC: U902.6, U902.12, U902.15
/PEX_0V9: C9011.1, C9012.1, C9013.1, C9014.1, L901.2, L902.1, R9008.2, U1.AA2, U1.AA4, U1.AA6, U1.AA8, U1.AA10, U1.AA12, U1.AB7, U1.AB13, U1.AB25, U1.AB31, U1.AC2, U1.AC20, U1.AC22, U1.AC24, U1.AC26, U1.AC28, U1.AC30, U1.AE2, U1.AE4, U1.AE6, U1.AE8, U1.AE10, U1.AE22, U1.AE24, U1.AE26, U1.AE28, U1.AE30, U1.AF1, U1.AG2, U1.AG4, U1.AG6, U1.AG8, U1.AG10, U1.AG24, U1.AG26, U1.AG28, U1.AG30, U1.AH1, U1.AH7, U1.U6, U1.U8, U1.U10, U1.U24, U1.U26, U1.V25, U1.V27, U1.V29, U1.V31, U1.W2, U1.W4, U1.W30, U1.Y1, U1.Y3, U1.Y5, U1.Y7, U1.Y9, U605.5, U901.40
/PEX_0V9A: C9015.1, C9016.1, L902.2, U1.AE20, U1.AF31, U1.AG12, U1.AG22, U1.AH13, U1.AJ6, U1.AJ10, U1.AJ14, U1.AJ18, U1.AJ22, U1.AJ26, U1.AJ30, U1.AK9, U1.AK11, U1.AK13, U1.AK15, U1.AK17, U1.AK19, U1.AK29, U1.AL2, U1.AL6, U1.AL10, U1.AL14, U1.AL18, U1.AL22, U1.AL30, U1.AM5, U1.AM11, U1.AM17, U1.AM23, U1.AM29, U1.L10, U1.L14, U1.L22, U1.L28, U1.M1, U1.M23, U1.N2, U1.N6, U1.N10, U1.N26, U1.N30, U1.P1, U1.P5, U1.P11, U1.P23, U1.P25, U1.P27, U1.P29, U1.P31, U1.R6, U1.R10, U1.R28, U1.T1, U1.T5, U1.T9, U1.T25, U1.U4, U1.U28, U1.V23, U1.W6
/PEX_1V8: C9023.1, C9024.1, C9025.1, C9028.1, C9029.1, L903.1, R724.2, R9022.1, R9041.2, U1.AA22, U1.AA24, U1.AC4, U1.AC6, U1.AD1, U1.AD7, U1.AD13, U1.AD19, U1.AE12, U1.AE14, U1.AE18, U1.AF7, U1.AF13, U1.AF25, U1.AG14, U1.AG20, U1.AH19, U1.AJ4, U1.AJ8, U1.AJ12, U1.AJ16, U1.AJ20, U1.AJ24, U1.AJ28, U1.AK1, U1.AK7, U1.AK21, U1.AK27, U1.AK31, U1.AL4, U1.AL8, U1.AL12, U1.AL16, U1.AL20, U1.AL24, U1.M31, U1.N4, U1.N8, U1.N22, U1.N28, U1.N32, U1.P3, U1.P7, U1.R4, U1.R8, U1.R26, U1.R30, U1.T3, U1.T7, U1.T23, U1.T27, U1.T29, U1.T31, U1.V1, U1.V3, U1.V5, U1.V7, U1.V9, U1.W8, U1.W10, U1.W24, U1.W26, U1.Y23, U1.Y25, U1.Y27, U606.8, U902.5, U902.9, U902.10
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
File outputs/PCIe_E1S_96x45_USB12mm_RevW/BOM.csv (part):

Ref,Value,Footprint,Side,X_mm,Y_mm,Rotation_deg,Height_mm,DNP,Manufacturer,MPN,Voltage_Rating,Tolerance,Dielectric,Datasheet,Qualification
C1,10uF 25V X7R,C_1210_3225Metric,F,75.75,8.25,0.0,,no,,,,,,,
C101,10nF 25V,C_0201_DenseCourtyard_1p0x0p4,B,82.2,3.5,0.0,,no,,,,,,,
C102,100nF 50V,C_0603_1608Metric,F,75.6,11.2,0.0,,no,,,,,,,
C103,10uF 25V X7R / effective >=1uF,C_0603_1608Metric,B,82.5,5.0,0.0,,no,,,,,,,
C104,10nF 25V,C_0201_DenseCourtyard_1p0x0p4,B,89.4,3.5,0.0,,no,,,,,,,
C105,100nF 50V,C_0603_1608Metric,F,70.75,1.25,0.0,,no,,,,,,,
C106,10uF 25V X7R / effective >=1uF,C_0603_1608Metric,B,89.7,5.0,0.0,,no,,,,,,,
C107,10nF 25V,C_0201_DenseCourtyard_1p0x0p4,B,82.2,8.9,0.0,,no,,,,,,,
C108,100nF 50V,C_0603_1608Metric,F,61.0,1.25,0.0,,no,,,,,,,
C109,10uF 25V X7R / effective >=1uF,C_0603_1608Metric,B,82.5,10.4,0.0,,no,,,,,,,
C110,10nF 25V,C_0402_1005Metric,F,30.35,3.6,0.0,,no,,,,,,,
C111,100nF 50V,C_0603_1608Metric,F,57.75,1.25,0.0,,no,,,,,,,
C112,10uF 25V X7R / effective >=1uF,C_0603_1608Metric,F,30.35,5.8,0.0,,no,,,,,,,
C113,10nF 25V,C_0402_1005Metric,F,38.35,3.6,0.0,,no,,,,,,,
C114,100nF 50V,C_0603_1608Metric,F,67.5,1.25,0.0,,no,,,,,,,
C115,10uF 25V X7R / effective >=1uF,C_0603_1608Metric,F,38.35,5.8,0.0,,no,,,,,,,
C116,10nF 25V,C_0402_1005Metric,F,46.35,3.6,0.0,,no,,,,,,,
C117,100nF 50V,C_0603_1608Metric,F,89.75,1.25,0.0,,no,,,,,,,
C118,10uF 25V X7R / effective >=1uF,C_0603_1608Metric,F,46.35,5.8,0.0,,no,,,,,,,
C119,10nF 25V,C_0201_DenseCourtyard_1p0x0p4,B,89.4,8.9,0.0,,no,,,,,,,
C120,100nF 50V,C_0603_1608Metric,F,86.5,1.25,0.0,,no,,,,,,,
C121,10uF 25V X7R / effective >=1uF,C_0603_1608Metric,B,89.7,10.4,0.0,,no,,,,,,,
C122,10nF 25V,C_0201_DenseCourtyard_1p0x0p4,B,82.2,14.3,0.0,,no,,,,,,,
C123,100nF 50V,C_0603_1608Metric,F,64.25,1.25,0.0,,no,,,,,,,
C124,10uF 25V X7R / effective >=1uF,C_0603_1608Metric,B,82.5,15.8,0.0,,no,,,,,,,
C125,10nF 25V,C_0201_DenseCourtyard_1p0x0p4,B,89.4,14.3,0.0,,no,,,,,,,
C126,100nF 50V,C_0603_1608Metric,F,80.0,1.25,0.0,,no,,,,,,,
C127,10uF 25V X7R / effective >=1uF,C_0603_1608Metric,B,89.7,15.8,0.0,,no,,,,,,,
C128,10nF 25V,C_0402_1005Metric,F,30.35,10.1,0.0,,no,,,,,,,
C129,100nF 50V,C_0603_1608Metric,F,83.25,1.25,0.0,,no,,,,,,,
C130,10uF 25V X7R / effective >=1uF,C_0603_1608Metric,F,30.35,12.3,0.0,,no,,,,,,,
C131,10nF 25V,C_0402_1005Metric,F,38.35,10.1,0.0,,no,,,,,,,
C133,10uF 25V X7R / effective >=1uF,C_0603_1608Metric,F,38.35,12.3,0.0,,no,,,,,,,
C134,10nF 25V,C_0402_1005Metric,F,46.35,10.1,0.0,,no,,,,,,,
C136,10uF 25V X7R / effective >=1uF,C_0603_1608Metric,F,46.35,12.3,0.0,,no,,,,,,,
C2,10uF 25V X7R,C_1210_3225Metric,F,89.0,9.25,0.0,,no,,,,,,,
C301,10nF 25V,C_0402_1005Metric,F,55.1,3.6,0.0,,no,,,,,,,
C311,10uF 25V,C_0805_2012Metric,F,71.2,4.8,0.0,,no,,,,,,,
C312,100nF 50V,C_0402_1005Metric,F,71.2,2.8,0.0,,no,,,,,,,
C313,3.3nF 25V,C_0402_1005Metric,F,71.2,7.1,180.0,,no,,,,,,,
C314,47uF 16V,C_1210_3225Metric,F,61.0,10.7,0.0,,no,,,,,,,
C315,47uF 16V,C_1210_3225Metric,F,66.7,10.7,0.0,,no,,,,,,,
C4001,220nF 16V / GRM033R61C224KE14D,C_0201_0603Metric_DenseCourtyard_1p30x0p55,F,24.0,24.335,180.0,0.33,no,,,,,,,
C4002,220nF 16V / GRM033R61C224KE14D,C_0201_0603Metric_DenseCourtyard_1p30x0p55,F,24.0,24.935,180.0,0.33,no,,,,,,,
C4003,220nF 16V / GRM033R61C224KE14D,C_0201_0603Metric_DenseCourtyard_1p30x0p55,F,24.0,22.535,180.0,0.33,no,,,,,,,
C4004,220nF 16V / GRM033R61C224KE14D,C_0201_0603Metric_DenseCourtyard_1p30x0p55,F,24.0,23.134999,180.0,0.33,no,,,,,,,
C4005,220nF 16V / GRM033R61C224KE14D,C_0201_0603Metric_DenseCourtyard_1p30x0p55,F,24.0,20.735,180.0,0.33,no,,,,,,,
C4006,220nF 16V / GRM033R61C224KE14D,C_0201_0603Metric_DenseCourtyard_1p30x0p55,F,24.0,21.335,180.0,0.33,no,,,,,,,
C4007,220nF 16V / GRM033R61C224KE14D,C_0201_0603Metric_DenseCourtyard_1p30x0p55,F,24.0,18.935001,180.0,0.33,no,,,,,,,
C4008,220nF 16V / GRM033R61C224KE14D,C_0201_0603Metric_DenseCourtyard_1p30x0p55,F,24.0,19.535,180.0,0.33,no,,,,,,,
C4009,220nF 16V / GRM033R61C224KE14D,C_0201_0603Metric_DenseCourtyard_1p30x0p55,F,32.0,24.335,180.0,0.33,no,,,,,,,
C4010,220nF 16V / GRM033R61C224KE14D,C_0201_0603Metric_DenseCourtyard_1p30x0p55,F,32.0,24.935,180.0,0.33,no,,,,,,,
C4011,220nF 16V / GRM033R61C224KE14D,C_0201_0603Metric_DenseCourtyard_1p30x0p55,F,32.0,22.535,180.0,0.33,no,,,,,,,
C4012,220nF 16V / GRM033R61C224KE14D,C_0201_0603Metric_DenseCourtyard_1p30x0p55,F,32.0,23.134999,180.0,0.33,no,,,,,,,
C4013,220nF 16V / GRM033R61C224KE14D,C_0201_0603Metric_DenseCourtyard_1p30x0p55,F,32.0,20.735,180.0,0.33,no,,,,,,,
C4014,220nF 16V / GRM033R61C224KE14D,C_0201_0603Metric_DenseCourtyard_1p30x0p55,F,32.0,21.335,180.0,0.33,no,,,,,,,
C4015,220nF 16V / GRM033R61C224KE14D,C_0201_0603Metric_DenseCourtyard_1p30x0p55,F,32.0,18.935001,180.0,0.33,no,,,,,,,
C4016,220nF 16V / GRM033R61C224KE14D,C_0201_0603Metric_DenseCourtyard_1p30x0p55,F,32.0,19.535,180.0,0.33,no,,,,,,,
C4017,220nF 16V / GRM033R61C224KE14D,C_0201_0603Metric_DenseCourtyard_1p30x0p55,F,40.0,24.335,180.0,0.33,no,,,,,,,
C4018,220nF 16V / GRM033R61C224KE14D,C_0201_0603Metric_DenseCourtyard_1p30x0p55,F,40.0,24.935,180.0,0.33,no,,,,,,,
C4019,220nF 16V / GRM033R61C224KE14D,C_0201_0603Metric_DenseCourtyard_1p30x0p55,F,40.0,22.535,180.0,0.33,no,,,,,,,
C4020,220nF 16V / GRM033R61C224KE14D,C_0201_0603Metric_DenseCourtyard_1p30x0p55,F,40.0,23.134999,180.0,0.33,no,,,,,,,
C4021,220nF 16V / GRM033R61C224KE14D,C_0201_0603Metric_DenseCourtyard_1p30x0p55,F,40.0,20.735,180.0,0.33,no,,,,,,,
C4022,220nF 16V / GRM033R61C224KE14D,C_0201_0603Metric_DenseCourtyard_1p30x0p55,F,40.0,21.335,180.0,0.33,no,,,,,,,
C4023,220nF 16V / GRM033R61C224KE14D,C_0201_0603Metric_DenseCourtyard_1p30x0p55,F,40.0,18.935001,180.0,0.33,no,,,,,,,
C4024,220nF 16V / GRM033R61C224KE14D,C_0201_0603Metric_DenseCourtyard_1p30x0p55,F,40.0,19.535,180.0,0.33,no,,,,,,,
C4025,220nF 16V / GRM033R61C224KE14D,C_0201_0603Metric_DenseCourtyard_1p30x0p55,F,48.0,24.335,180.0,0.33,no,,,,,,,
C4026,220nF 16V / GRM033R61C224KE14D,C_0201_0603Metric_DenseCourtyard_1p30x0p55,F,48.0,24.935,180.0,0.33,no,,,,,,,
C4027,220nF 16V / GRM033R61C224KE14D,C_0201_0603Metric_DenseCourtyard_1p30x0p55,F,48.0,22.535,180.0,0.33,no,,,,,,,
C4028,220nF 16V / GRM033R61C224KE14D,C_0201_0603Metric_DenseCourtyard_1p30x0p55,F,48.0,23.134999,180.0,0.33,no,,,,,,,
C4029,220nF 16V / GRM033R61C224KE14D,C_0201_0603Metric_DenseCourtyard_1p30x0p55,F,48.0,20.735,180.0,0.33,no,,,,,,,
C4030,220nF 16V / GRM033R61C224KE14D,C_0201_0603Metric_DenseCourtyard_1p30x0p55,F,48.0,21.335,180.0,0.33,no,,,,,,,
C4031,220nF 16V / GRM033R61C224KE14D,C_0201_0603Metric_DenseCourtyard_1p30x0p55,F,48.0,18.935001,180.0,0.33,no,,,,,,,
C4032,220nF 16V / GRM033R61C224KE14D,C_0201_0603Metric_DenseCourtyard_1p30x0p55,F,48.0,19.535,180.0,0.33,no,,,,,,,
C4033,220nF 16V / GRM033R61C224KE14D,C_0201_0603Metric_DenseCourtyard_1p30x0p55,F,56.0,24.335,180.0,0.33,no,,,,,,,
C4034,220nF 16V / GRM033R61C224KE14D,C_0201_0603Metric_DenseCourtyard_1p30x0p55,F,56.0,24.935,180.0,0.33,no,,,,,,,
C4035,220nF 16V / GRM033R61C224KE14D,C_0201_0603Metric_DenseCourtyard_1p30x0p55,F,56.0,22.535,180.0,0.33,no,,,,,,,
C4036,220nF 16V / GRM033R61C224KE14D,C_0201_0603Metric_DenseCourtyard_1p30x0p55,F,56.0,23.134999,180.0,0.33,no,,,,,,,
C4037,220nF 16V / GRM033R61C224KE14D,C_0201_0603Metric_DenseCourtyard_1p30x0p55,F,56.0,20.735,180.0,0.33,no,,,,,,,
C4038,220nF 16V / GRM033R61C224KE14D,C_0201_0603Metric_DenseCourtyard_1p30x0p55,F,56.0,21.335,180.0,0.33,no,,,,,,,
C4039,220nF 16V / GRM033R61C224KE14D,C_0201_0603Metric_DenseCourtyard_1p30x0p55,F,56.0,18.935001,180.0,0.33,no,,,,,,,
C4040,220nF 16V / GRM033R61C224KE14D,C_0201_0603Metric_DenseCourtyard_1p30x0p55,F,56.0,19.535,180.0,0.33,no,,,,,,,
C4041,220nF 16V / GRM033R61C224KE14D,C_0201_0603Metric_DenseCourtyard_1p30x0p55,F,64.0,24.335,180.0,0.33,no,,,,,,,
C4042,220nF 16V / GRM033R61C224KE14D,C_0201_0603Metric_DenseCourtyard_1p30x0p55,F,64.0,24.935,180.0,0.33,no,,,,,,,
C4043,220nF 16V / GRM033R61C224KE14D,C_0201_0603Metric_DenseCourtyard_1p30x0p55,F,64.0,22.535,180.0,0.33,no,,,,,,,
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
